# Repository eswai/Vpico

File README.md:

# Vpico

Vpico is a 40-key ortholinear keyboard powered by Raspberry Pi Pico, PicoRuby and PRK-Firmware.

#  BOM

|Name | Part number|Quantity|
|------|-----|-----|
| MCU | Raspberry Pi Pico | 1|
| PCB | Vpico PCB | 1|
| Case | Vpico.step | 1|
| MX-compaible key switch or Kailh Choc key switch | 5pins | 40|
| Diode | 1N4148 TH or SMD  | 40|
| Screw | M2 L4mm | 5|
| Keycap 18x17 | 1U | 38|
| Keycap 27x17 | 1.5U | 2|
| LED | SK6812MINI-E | 1|
| Adhesive rubber feet | Dia.9mm or smaller | 4|

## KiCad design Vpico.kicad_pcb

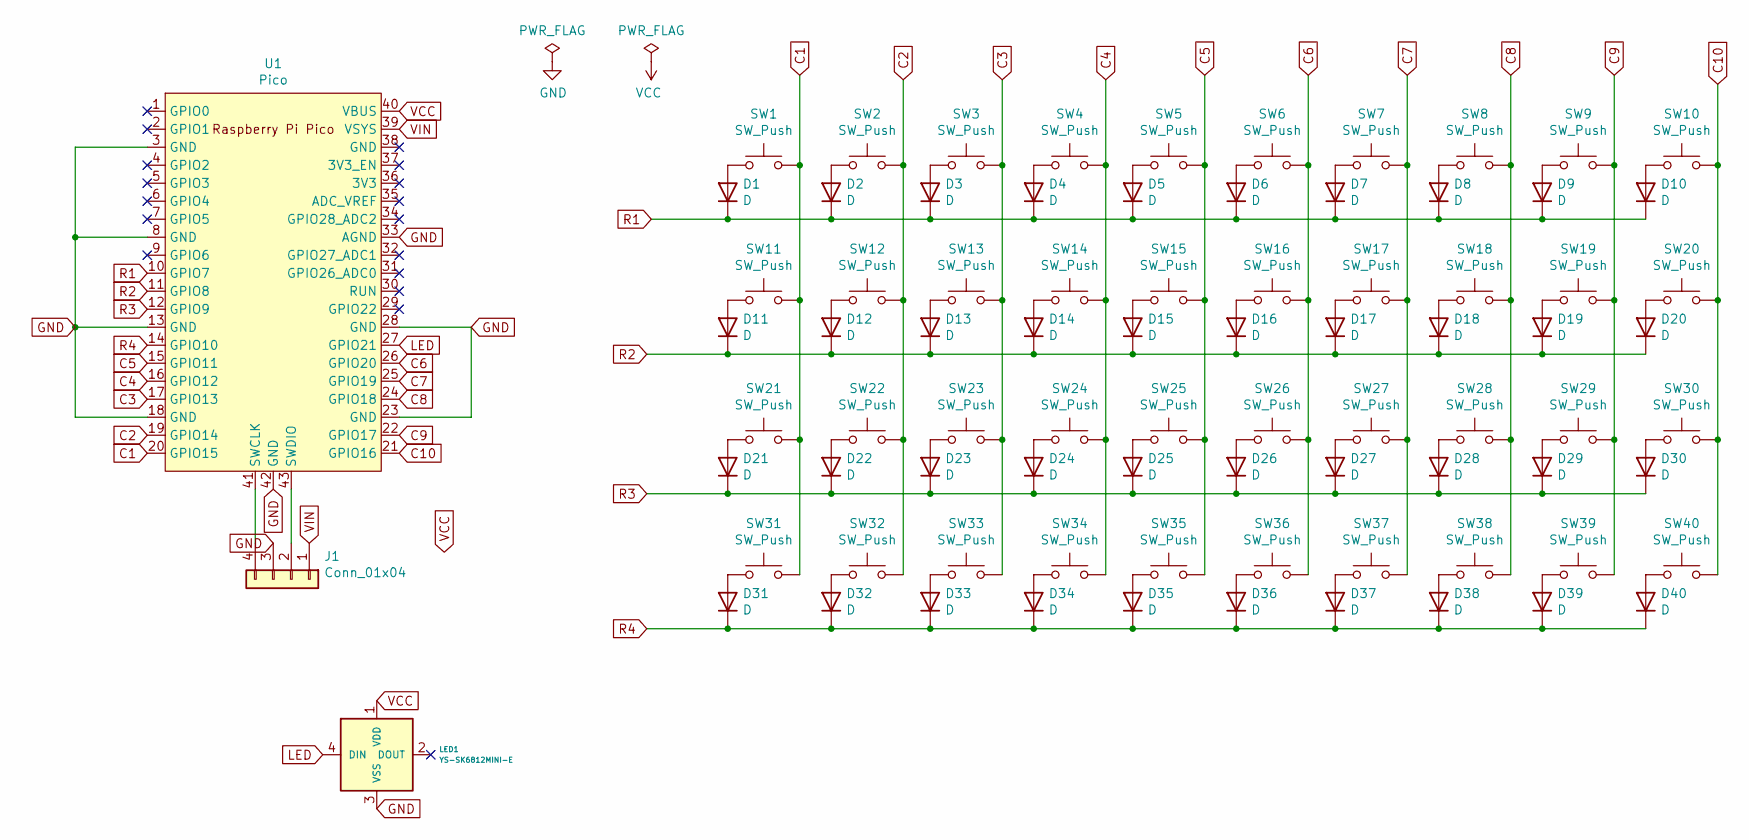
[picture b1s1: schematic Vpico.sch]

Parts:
D1, D2, D3, D4, D5, D6, D7, D8, D9, D10, D11, D12, D13, D14, D15, D16, D17, D18, D19, D20, D21, D22, D23, D24, D25, D26, D27, D28, D29, D30, D31, D32, D33, D34, D35, D36, D37, D38, D39, D40: D; D_SOD-123
J1: Conn_01x04; PinHeader_1x04_P2.54mm_Vertical
LED1: YS-SK6812MINI-E
SW1, SW2, SW3, SW4, SW5, SW6, SW7, SW8, SW9, SW10, SW11, SW12, SW13, SW14, SW15, SW16, SW17, SW18, SW19, SW20, SW21, SW22, SW23, SW24, SW25, SW26, SW27, SW28, SW29, SW30, SW31, SW32, SW33, SW34, SW37, SW38, SW39, SW40: SW_Push; CherryMX_Choc_1u
SW35, SW36: SW_Push; CherryMX_Choc_1.5u
U1: Pico; RPi_Pico_SMD_TH

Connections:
C1: SW1.2, SW11.2, SW21.2, SW31.2, U1.20 (GPIO15)
C2: SW2.2, SW12.2, SW22.2, SW32.2, U1.19 (GPIO14)
C3: SW3.2, SW13.2, SW23.2, SW33.2, U1.17 (GPIO13)
C4: SW4.2, SW14.2, SW24.2, SW34.2, U1.16 (GPIO12)
C5: SW5.2, SW15.2, SW25.2, SW35.2, U1.15 (GPIO11)
C6: SW6.2, SW16.2, SW26.2, SW36.2, U1.26 (GPIO20)
C7: SW7.2, SW17.2, SW27.2, SW37.2, U1.25 (GPIO19)
C8: SW8.2, SW18.2, SW28.2, SW38.2, U1.24 (GPIO18)
C9: SW9.2, SW19.2, SW29.2, SW39.2, U1.22 (GPIO17)
C10: SW10.2, SW20.2, SW30.2, SW40.2, U1.21 (GPIO16)
GND: J1.3, LED1.3 (VSS), U1.3 (GND), U1.8 (GND), U1.13 (GND), U1.18 (GND), U1.23 (GND), U1.28 (GND), U1.33 (AGND), U1.42 (GND)
LED: LED1.4 (DIN), U1.27 (GPIO21)
unnamed: D1.2 (A), SW1.1
unnamed: D2.2 (A), SW2.1
unnamed: D3.2 (A), SW3.1
unnamed: D4.2 (A), SW4.1
unnamed: D5.2 (A), SW5.1
unnamed: D6.2 (A), SW6.1
unnamed: D7.2 (A), SW7.1
unnamed: D8.2 (A), SW8.1
unnamed: D9.2 (A), SW9.1
unnamed: D10.2 (A), SW10.1
unnamed: D11.2 (A), SW11.1
unnamed: D12.2 (A), SW12.1
unnamed: D13.2 (A), SW13.1
unnamed: D14.2 (A), SW14.1
unnamed: D15.2 (A), SW15.1
unnamed: D16.2 (A), SW16.1
unnamed: D17.2 (A), SW17.1
unnamed: D18.2 (A), SW18.1
unnamed: D19.2 (A), SW19.1
unnamed: D20.2 (A), SW20.1
unnamed: D21.2 (A), SW21.1
unnamed: D22.2 (A), SW22.1
unnamed: D23.2 (A), SW23.1
unnamed: D24.2 (A), SW24.1
unnamed: D25.2 (A), SW25.1
unnamed: D26.2 (A), SW26.1
unnamed: D27.2 (A), SW27.1
unnamed: D28.2 (A), SW28.1
unnamed: D29.2 (A), SW29.1
unnamed: D30.2 (A), SW30.1
unnamed: D31.2 (A), SW31.1
unnamed: D32.2 (A), SW32.1
unnamed: D33.2 (A), SW33.1
unnamed: D34.2 (A), SW34.1
unnamed: D35.2 (A), SW35.1
unnamed: D36.2 (A), SW36.1
unnamed: D37.2 (A), SW37.1
unnamed: D38.2 (A), SW38.1
unnamed: D39.2 (A), SW39.1
unnamed: D40.2 (A), SW40.1
unnamed: J1.2, U1.43 (SWDIO)
unnamed: J1.4, U1.41 (SWCLK)
R1: D1.1 (K), D2.1 (K), D3.1 (K), D4.1 (K), D5.1 (K), D6.1 (K), D7.1 (K), D8.1 (K), D9.1 (K), D10.1 (K), U1.10 (GPIO7)
R2: D11.1 (K), D12.1 (K), D13.1 (K), D14.1 (K), D15.1 (K), D16.1 (K), D17.1 (K), D18.1 (K), D19.1 (K), D20.1 (K), U1.11 (GPIO8)
R3: D21.1 (K), D22.1 (K), D23.1 (K), D24.1 (K), D25.1 (K), D26.1 (K), D27.1 (K), D28.1 (K), D29.1 (K), D30.1 (K), U1.12 (GPIO9)
R4: D31.1 (K), D32.1 (K), D33.1 (K), D34.1 (K), D35.1 (K), D36.1 (K), D37.1 (K), D38.1 (K), D39.1 (K), D40.1 (K), U1.14 (GPIO10)
VCC: LED1.1 (VDD), U1.40 (VBUS)
VIN: J1.1, U1.39 (VSYS)

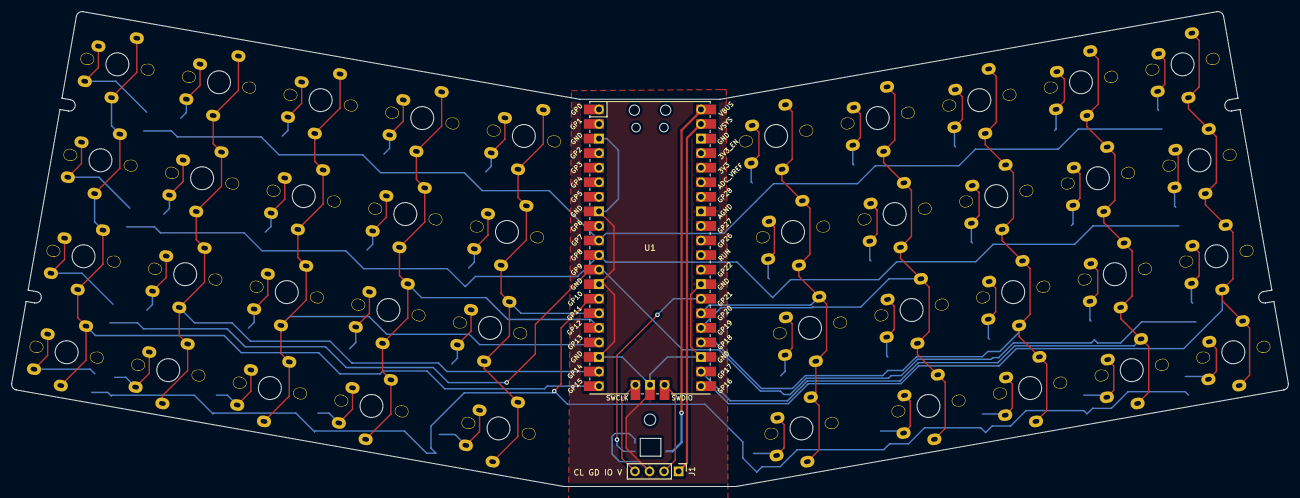
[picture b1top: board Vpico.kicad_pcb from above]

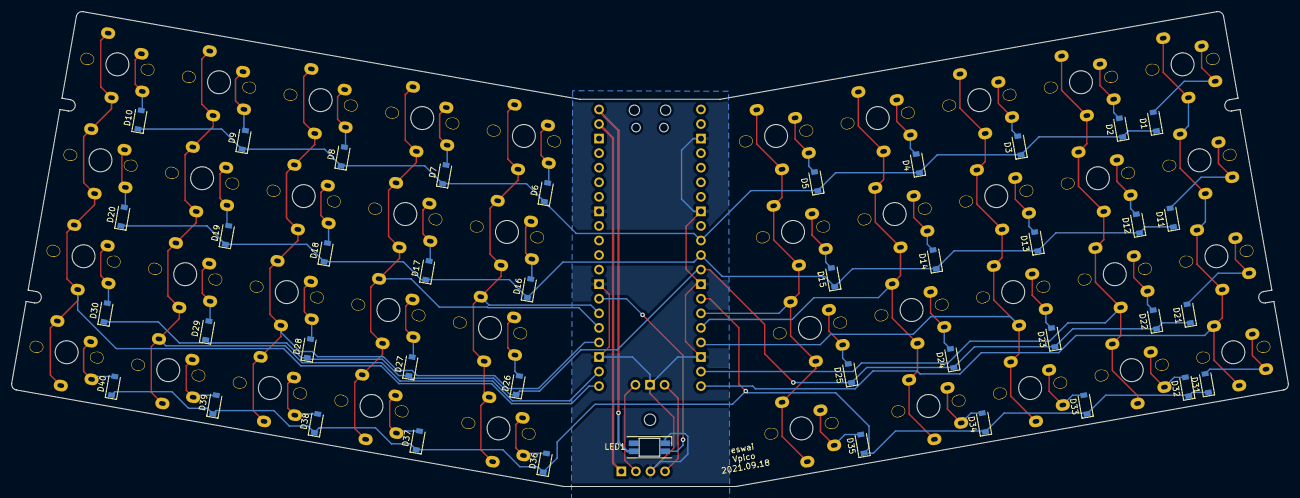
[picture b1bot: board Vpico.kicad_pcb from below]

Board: 2 copper layers, 222.7 x 82.8 mm, 83 parts (41 on the bottom side), 60 nets.
